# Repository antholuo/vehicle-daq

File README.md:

# vehicle-daq

Vehicle data-acquisition system: **ESP32-C6 sensor nodes** stream IMU and GPS over **ESP-NOW** to a **bridge**; the bridge forwards data over **USB** to a **Raspberry Pi**, which logs CSV, runs optional AHRS, and supports **track capture** (waypoint logging via a GPS-only “floating” node).

**note:** Correspondent REPLAY system is hosted here: https://github.com/Trotyl15/vehicle-replay

The two main software pieces are:

| Component | Location | Role |
|-----------|----------|------|
| **rpi_rx_rust** | [`sw/tools/rpi_rx_rust/`](sw/tools/rpi_rx_rust/) | Pi-side: COBS decoder, CSV logging, AHRS, track capture (GPIO or interactive). |
| **sensor_board_rev1_test** | [`sw/sensor_board/sensor_board_rev1_test/`](sw/sensor_board/sensor_board_rev1_test/) | Firmware for Rev1 DAQ nodes (sensor + floating) and for the bridge (devkit). |

---

## System overview

```mermaid
flowchart TB
  subgraph sensors["Sensor nodes"]
    SN["rev1_board<br/>IMU + GPS"]
  end

  subgraph bridge["Bridge (devkit)"]
    B["devkit_c<br/>Forward, TimeSync<br/>track heartbeats"]
  end

  subgraph host["Raspberry Pi"]
    R["rpi_rx_rust<br/>Logs, AHRS<br/>track capture"]
  end

  subgraph floating["Floating node"]
    F["sensorboard_floating<br/>GPS only"]
  end

  SN -->|"ESP-NOW (IMU, GPS, heartbeat)"| B
  B -->|"USB COBS (forwarded messages)"| R
  R -->|"TimeSync, Arm/End, RequestFloatingGps"| B
  B -->|"TrackCaptureArmed/Ended (pause TX)"| SN
  B -->|"RequestGpsCapture"| F
  F -->|"5× GPS reply"| B
  B -->|"heartbeat 0xFE (when armed)"| R
```

- **Sensor nodes** (`rev1_board`): Read IMU and GPS, send over ESP-NOW. When track capture is armed, they pause so the floating node’s packets aren’t dropped.
- **Bridge** (`devkit_c`): Receives ESP-NOW, assigns node IDs by MAC, forwards messages to the Pi over USB (COBS). Sends TimeSync to nodes; handles Arm/End track and RequestFloatingGps; when armed, sends a track-capture heartbeat (0xFE) to the Pi every 500 ms.
- **Floating node** (`sensorboard_floating`): GPS-only; on RequestGpsCapture it replies with the next 5 GPS samples for waypoint logging.
- **Pi** (`rpi_rx_rust`): Decodes COBS stream, writes raw CSV (and optional AHRS CSV). Can arm track capture, request floating GPS per waypoint, and write track files (`~/daq/tracks/<date>/<time>.csv`). Uses track heartbeats to auto-end capture if the bridge disappears; bridge auto-ends if the Pi disappears.

---

## Raspberry Pi (rpi_rx_rust)

- **Binaries**: `rpi_rx_rust` (CLI + serial), `rpi_rx_rust_gpio` (GPIO-only service), `rpi_rx_rust_track_test` (interactive track capture), `ahrs_postprocess`, `gps_extract`.
- **Default serial**: `/dev/ttyACM0`, 115200 baud (set `RPI_RX_SERIAL_PORT` if the bridge is on another port).
- **Logs**: `~/daq/logs/<date>/` (raw and AHRS); track files: `~/daq/tracks/<date>/`.
- **Track capture**: Arm → take location (request 5 GPS from floating node, average, append one row) → end. Heartbeat from bridge (0xFE) every 500 ms; 3 s without heartbeat or 2 s without USB from Pi triggers auto-end.

Full build and usage: **[sw/tools/rpi_rx_rust/README.md](sw/tools/rpi_rx_rust/README.md)**.

---

## Sensor board & bridge (sensor_board_rev1_test)

- **Binaries**: `rev1_board` (sensor node), `devkit_c` (bridge), `sensorboard_floating` (GPS-only for track capture).
- **Build** (from `sw/sensor_board/sensor_board_rev1_test/`):
  - Sensor: `cargo build --bin rev1_board` (optional `--features pos_center` etc.).
  - Bridge: `cargo build --bin devkit_c --no-default-features --features bridge`.
  - Floating: `cargo build --bin sensorboard_floating --no-default-features --features floating`.
- **HMI**: User LED (1 Hz) + NeoPixel (state/feedback). Bridge: 4× blink when armed; orange when sending request; green/rainbow on success/timeout. Floating: green breathing when idle with fix; orange when acquiring.

Full build, features, task model, and hardware init: **[sw/sensor_board/sensor_board_rev1_test/README.md](sw/sensor_board/sensor_board_rev1_test/README.md)**.

Other repos under `sw/`, `ee/`, and `vision/` may have their own READMEs.

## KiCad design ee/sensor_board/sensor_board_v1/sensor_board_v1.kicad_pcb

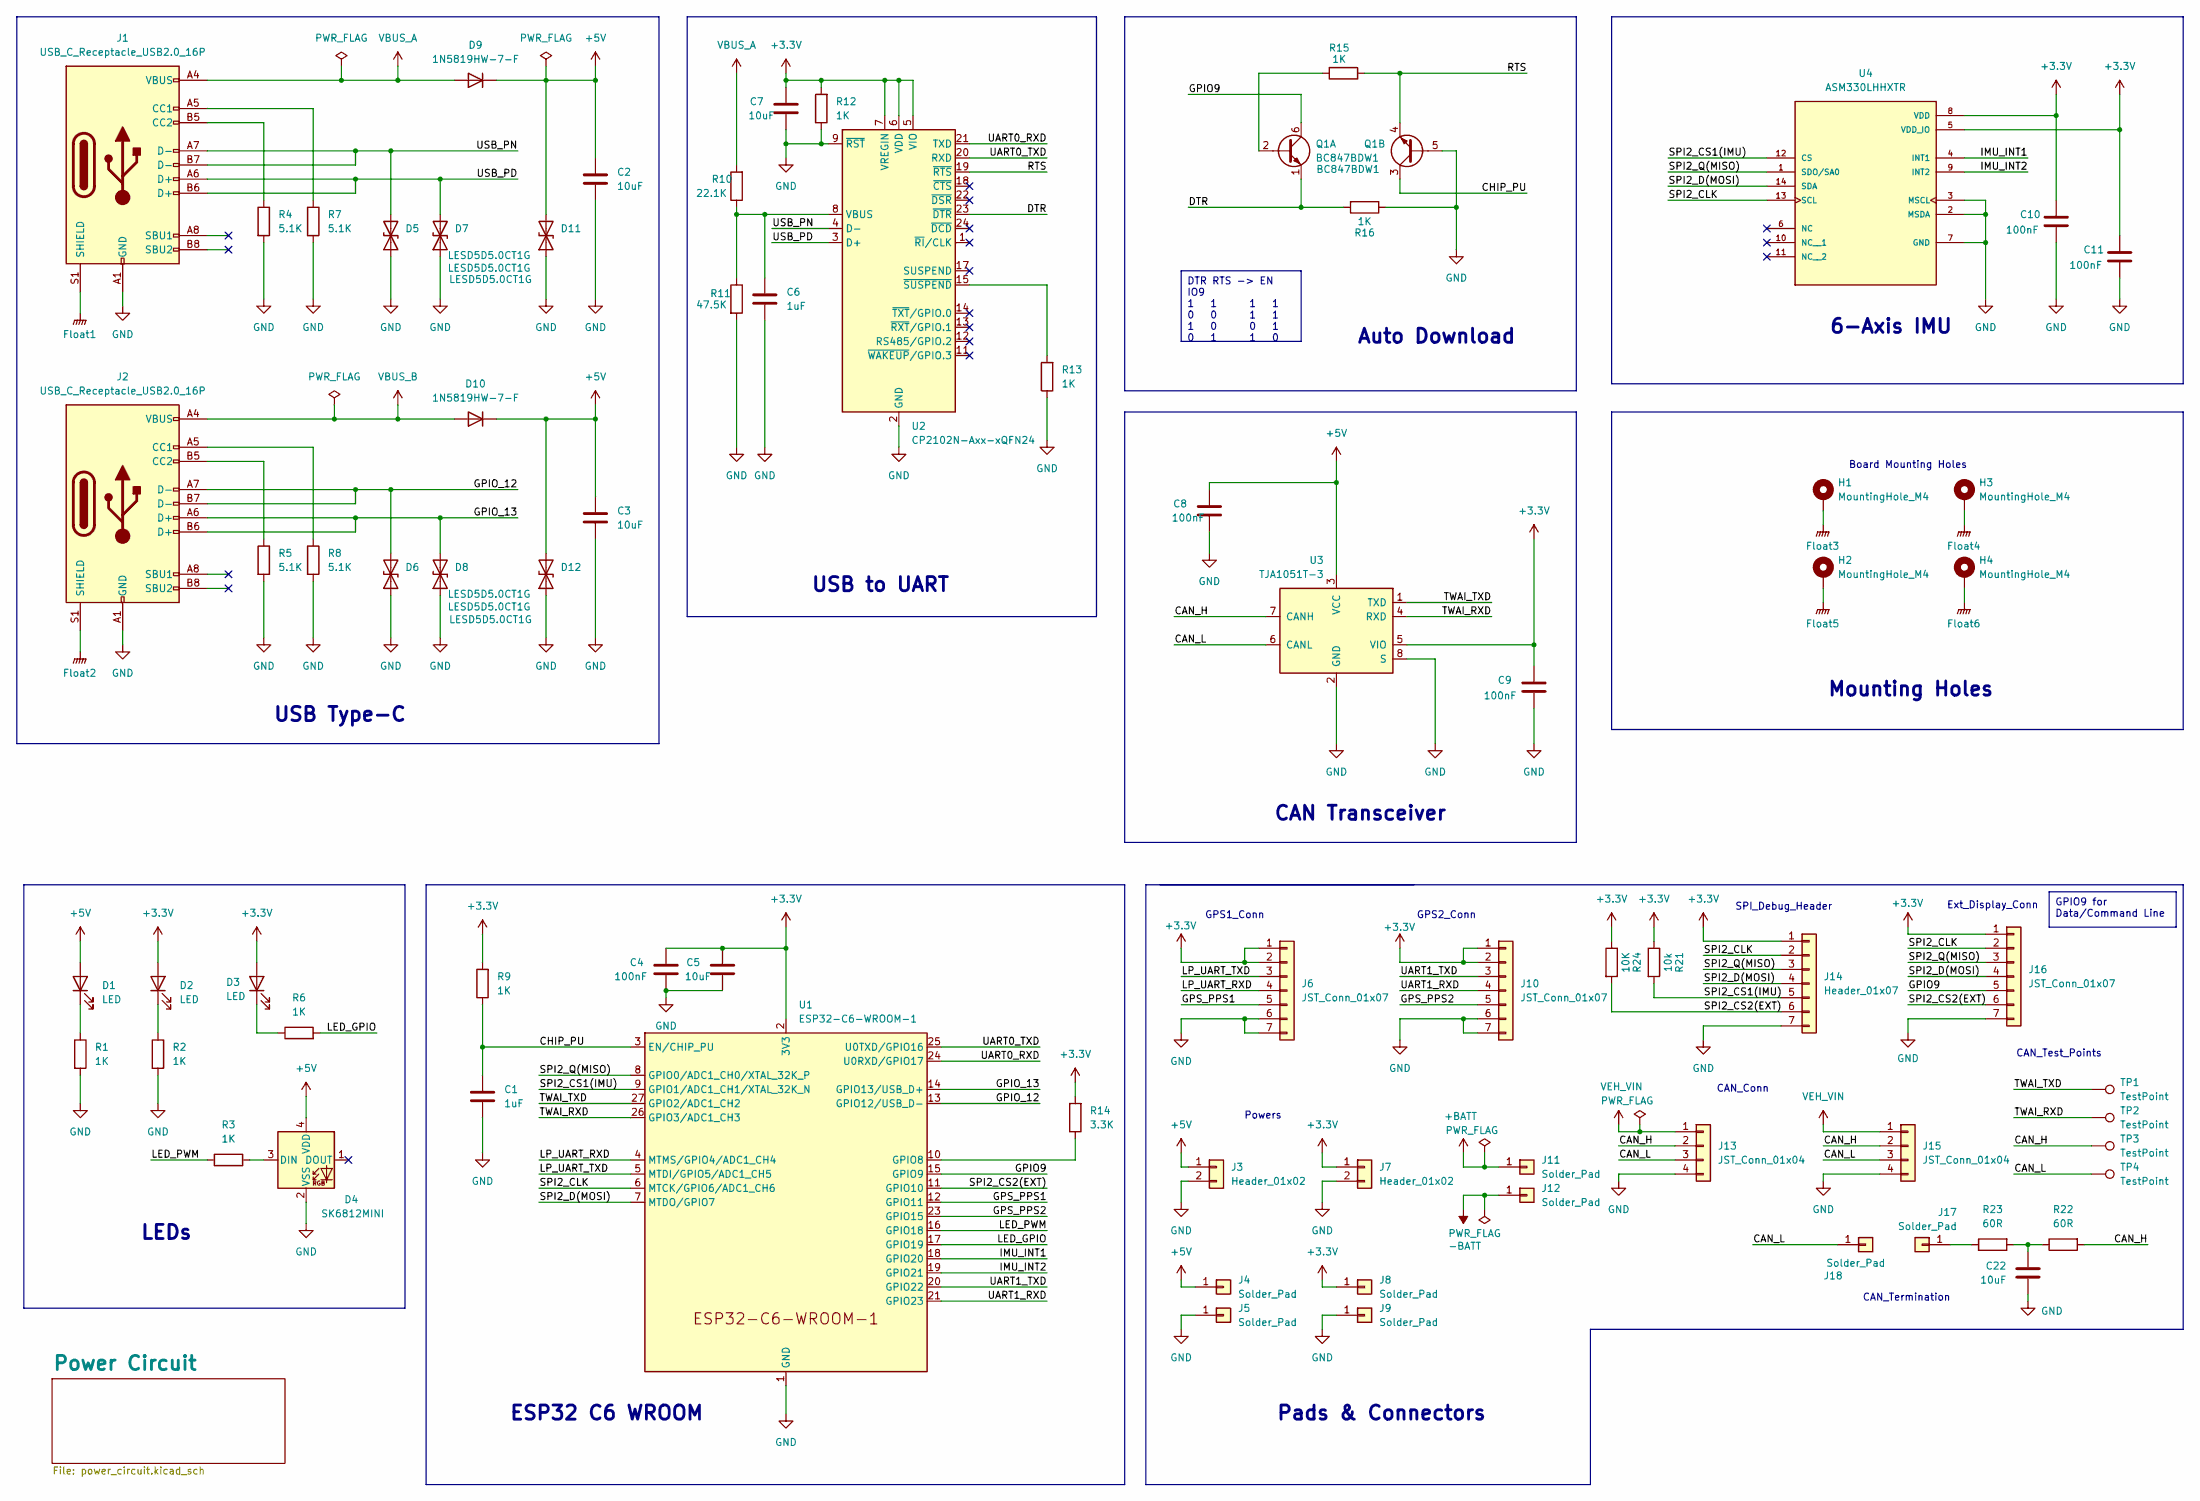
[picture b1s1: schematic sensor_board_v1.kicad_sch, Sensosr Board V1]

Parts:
C1, C6: 1uF; C_0603_1608Metric
C2, C3, C5, C7, C22: 10uF; C_0603_1608Metric
C4, C8, C9, C10, C11: 100nF; C_0603_1608Metric
D1, D2, D3: LED; LED_0603_1608Metric
D4: SK6812MINI; LED_SK6812MINI_PLCC4_3.5x3.5mm_P1.75mm
D5, D6, D7, D8, D11, D12: LESD5D5.0CT1G; D_0603_1608Metric
D9, D10: 1N5819HW-7-F; D_SOD-123
H1, H2, H3, H4: MountingHole_M4; MountingHole_4.3mm_M4_DIN965_Pad
J1, J2: USB_C_Receptacle_USB2.0_16P; USB_C_Receptacle_Palconn_UTC16-G
J3, J7: Header_01x02; PinHeader_1x02_P1.00mm_Vertical
J4, J5, J8, J9, J17, J18: Solder_Pad; SolderWirePad_1x01_SMD_1x2mm
J6, J10, J16: JST_Conn_01x07; JST_GH_SM07B-GHS-TB_1x07-1MP_P1.25mm_Horizontal
J11, J12: Solder_Pad; TestPoint_Pad_2.0x2.0mm
J13, J15: JST_Conn_01x04; JST_GH_SM04B-GHS-TB_1x04-1MP_P1.25mm_Horizontal
J14: Header_01x07; JST_GH_SM07B-GHS-TB_1x07-1MP_P1.25mm_Horizontal
Q1: BC847BDW1; SOT-363_SC-70-6
R1, R2, R3, R6, R9, R12, R13, R15, R16: 1K; R_0603_1608Metric
R4, R5, R7, R8: 5.1K; R_0603_1608Metric
R10: 22.1K; R_0603_1608Metric
R11: 47.5K; R_0603_1608Metric
R14: 3.3K; R_0603_1608Metric
R21: 10k; R_0603_1608Metric
R22, R23: 60R; R_0603_1608Metric
R24: 10K; R_0603_1608Metric
TP1, TP2, TP3, TP4: TestPoint; TestPoint_Pad_1.0x1.0mm
U1: ESP32-C6-WROOM-1
U2: CP2102N-Axx-xQFN24; QFN-24-1EP_4x4mm_P0.5mm_EP2.6x2.6mm
U3: TJA1051T-3; SOIC-8_3.9x4.9mm_P1.27mm
U4: ASM330LHHXTR; XDCR_ASM330LHHXTR; PARTREV 8

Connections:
+3.3V: C4.1, C5.1, C7.1, C9.1, C10.1, C11.1, D2.2 (A), D3.2 (A), J6.1, J6.2, J7.1, J8.1, J10.1, J10.2, J14.1, J16.1, R9.2, R12.2, R14.2, R21.1, R24.1, U1.2 (3V3), U2.5 (VIO), U2.6 (VDD), U2.7 (VREGIN), U3.5 (VIO), U4.5 (VDD_IO), U4.8 (VDD); also elsewhere on the board
+5V: C2.1, C3.1, C8.1, D1.2 (A), D4.4 (VDD), D9.1 (K), D10.1 (K), D11.2 (A2), D12.2 (A2), J3.1, J4.1, U3.3 (VCC); also elsewhere on the board
+BATT: J11.1; also elsewhere on the board
-BATT: J12.1; also elsewhere on the board
/CAN_H: J13.2, J15.2, R22.2, TP3.1, U3.7 (CANH)
/CAN_L: J13.3, J15.3, J18.1, TP4.1, U3.6 (CANL)
/CHIP_PU: C1.1, Q1.3 (C2), R9.1, U1.3 (EN/CHIP_PU)
/DTR: Q1.1 (E1), R16.2, U2.23 (~DTR)
/GPIO9: J16.5, Q1.6 (C1), U1.15 (GPIO9)
/GPIO_12: D6.2 (A2), J2.A7 (D-), J2.B7 (D-), U1.13 (GPIO12/USB_D-)
/GPIO_13: D8.2 (A2), J2.A6 (D+), J2.B6 (D+), U1.14 (GPIO13/USB_D+)
/GPS_PPS1: J6.5, U1.12 (GPIO11)
/GPS_PPS2: J10.5, U1.23 (GPIO15)
/IMU_INT1: U1.18 (GPIO20), U4.4 (INT1)
/IMU_INT2: U1.19 (GPIO21), U4.9 (INT2)
/LED_GPIO: R6.2, U1.17 (GPIO19)
/LED_PWM: R3.1, U1.16 (GPIO18)
/LP_UART_RXD: J6.4, U1.4 (MTMS/GPIO4/ADC1_CH4)
/LP_UART_TXD: J6.3, U1.5 (MTDI/GPIO5/ADC1_CH5)
/RTS: Q1.4 (E2), R15.1, U2.19 (~RTS)
/SPI2_CLK: J14.2, J16.2, U1.6 (MTCK/GPIO6/ADC1_CH6), U4.13 (SCL)
/SPI2_CS1(IMU): J14.5, R21.2, U1.9 (GPIO1/ADC1_CH1/XTAL_32K_N), U4.12 (CS)
/SPI2_CS2(EXT): J14.6, J16.6, R24.2, U1.11 (GPIO10)
/SPI2_D(MOSI): J14.4, J16.4, U1.7 (MTDO/GPIO7), U4.14 (SDA)
/SPI2_Q(MISO): J14.3, J16.3, U1.8 (GPIO0/ADC1_CH0/XTAL_32K_P), U4.1 (SDO/SA0)
/TWAI_RXD: TP2.1, U1.26 (GPIO3/ADC1_CH3), U3.4 (RXD)
/TWAI_TXD: TP1.1, U1.27 (GPIO2/ADC1_CH2), U3.1 (TXD)
/UART0_RXD: U1.24 (U0RXD/GPIO17), U2.21 (TXD)
/UART0_TXD: U1.25 (U0TXD/GPIO16), U2.20 (RXD)
/UART1_RXD: J10.4, U1.21 (GPIO23)
/UART1_TXD: J10.3, U1.20 (GPIO22)
/USB_PD: D7.2 (A2), J1.A6 (D+), J1.B6 (D+), U2.3 (D+)
/USB_PN: D5.2 (A2), J1.A7 (D-), J1.B7 (D-), U2.4 (D-)
Float1: J1.S1 (SHIELD)
Float2: J2.S1 (SHIELD)
Float3: H1.1
Float4: H3.1
Float5: H2.1
Float6: H4.1
GND: C1.2, C2.2, C3.2, C4.2, C5.2, C6.2, C7.2, C8.2, C9.2, C10.2, C11.2, C22.2, D4.2 (VSS), D5.1 (A1), D6.1 (A1), D7.1 (A1), D8.1 (A1), D11.1 (A1), D12.1 (A1), J1.A1 (GND), J1.A12 (GND), J1.B1 (GND), J1.B12 (GND), J2.A1 (GND), J2.A12 (GND), J2.B1 (GND), J2.B12 (GND), J3.2, J5.1, J6.6, J6.7, J7.2, J9.1, J10.6, J10.7, J13.4, J14.7, J15.4, J16.7, Q1.5 (B2), R1.2, R2.2, R4.2, R5.2, R7.2, R8.2, R11.2, R12.1, R13.1, R16.1, U1.1 (GND), U1.28 (GND), U1.29 (GND), U2.2 (GND), U2.9 (~RST), U2.25 (GND), U3.2 (GND), U3.8 (S), U4.2 (MSDA), U4.3 (MSCL), U4.7 (GND); also elsewhere on the board
unnamed: C22.1, R22.1, R23.2
unnamed: D1.1 (K), R1.1
unnamed: D2.1 (K), R2.1
unnamed: D3.1 (K), R6.1
unnamed: D4.3 (DIN), R3.2
unnamed: J1.A5 (CC1), R7.1
unnamed: J1.B5 (CC2), R4.1
unnamed: J2.A5 (CC1), R8.1
unnamed: J2.B5 (CC2), R5.1
unnamed: J17.1, R23.1
unnamed: Q1.2 (B1), R15.2
unnamed: R14.1, U1.10 (GPIO8)
unnamed: C6.1, R10.1, R11.1, U2.8 (VBUS)
unnamed: R13.2, U2.15 (~SUSPEND)
VBUS_A: D9.2 (A), J1.A4 (VBUS), J1.A9 (VBUS), J1.B4 (VBUS), J1.B9 (VBUS), R10.2
VBUS_B: D10.2 (A), J2.A4 (VBUS), J2.A9 (VBUS), J2.B4 (VBUS), J2.B9 (VBUS)
VEH_VIN: J13.1, J15.1; also elsewhere on the board

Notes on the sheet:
GPIO9 for Data/Command Line
DTR RTS -> EN IO9 1 1 1 1 0 0 1 1 1 0 0 1 0 1 1 0
GPS1_Conn
USB to UART
6-Axis IMU
ESP32 C6 WROOM
Auto Download
Mounting Holes
Powers
SPI_Debug_Header
Ext_Display_Conn
USB Type-C
Board Mounting Holes
GPS2_Conn
CAN Transceiver
CAN_Conn
CAN_Test_Points
LEDs
Pads & Connectors
CAN_Termination

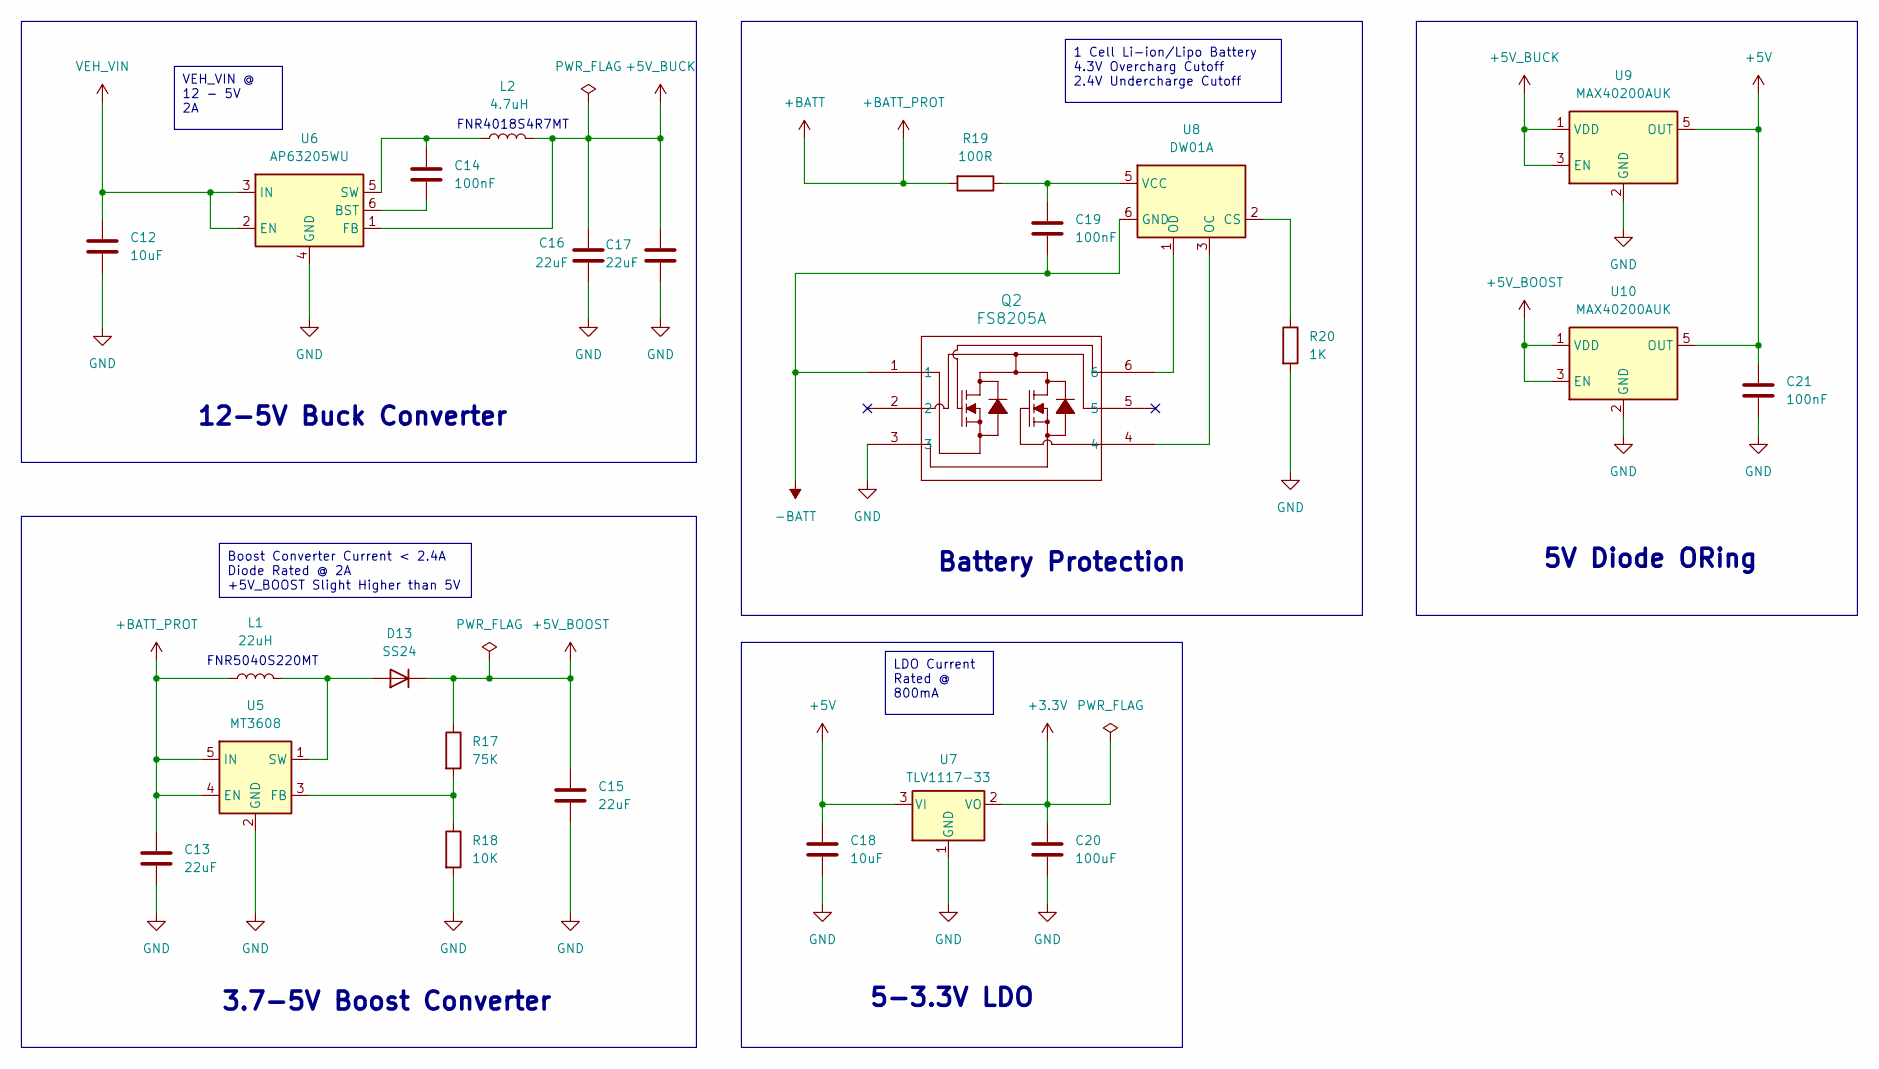
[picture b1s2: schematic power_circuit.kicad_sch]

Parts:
C12: 10uF; C_0805_2012Metric
C13, C15, C16, C17: 22uF; C_0805_2012Metric
C14, C19, C21: 100nF; C_0603_1608Metric
C18: 10uF; C_0603_1608Metric
C20: 100uF; C_0805_2012Metric
D13: SS24; D_SOD-123F
L1: 22uH; L_Changjiang_FNR5040S
L2: 4.7uH; L_Changjiang_FNR4018S
Q2: FS8205A; SOT-23-6L_TCP
R17: 75K; R_0603_1608Metric
R18: 10K; R_0603_1608Metric
R19: 100R; R_0603_1608Metric
R20: 1K; R_0603_1608Metric
U5: MT3608; SOT-23-6
U6: AP63205WU; TSOT-23-6
U7: TLV1117-33; SOT230P700X180-4N
U8: DW01A; SOT-23-6
U9, U10: MAX40200AUK; SOT-23-5

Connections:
+3.3V: C20.1, U7.2 (VO); also elsewhere on the board
+5V: C18.1, C21.1, U7.3 (VI), U9.5 (OUT), U10.5 (OUT); also elsewhere on the board
+5V_BOOST: C15.1, D13.1 (K), R17.1, U10.1 (VDD), U10.3 (EN)
+5V_BUCK: C16.1, C17.1, L2.2, U6.1 (FB), U9.1 (VDD), U9.3 (EN)
+BATT: C13.1, L1.1, R19.2, U5.4 (EN), U5.5 (IN); also elsewhere on the board
-BATT: C19.2, Q2.1, U8.6 (GND); also elsewhere on the board
GND: C12.2, C13.2, C15.2, C16.2, C17.2, C18.2, C20.2, C21.2, Q2.3, R18.2, R20.2, U5.2 (GND), U6.4 (GND), U7.1 (GND), U9.2 (GND), U10.2 (GND); also elsewhere on the board
unnamed: D13.2 (A), L1.2, U5.1 (SW)
unnamed: R17.2, R18.1, U5.3 (FB)
unnamed: C14.2, U6.6 (BST)
unnamed: C14.1, L2.1, U6.5 (SW)
unnamed: R20.1, U8.2 (CS)
unnamed: Q2.4, U8.3 (OC)
unnamed: Q2.6, U8.1 (OD)
unnamed: C19.1, R19.1, U8.5 (VCC)
VEH_VIN: C12.1, U6.2 (EN), U6.3 (IN); also elsewhere on the board

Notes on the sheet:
VEH_VIN @ 12 - 5V 2A
Boost Converter Current < 2.4A Diode Rated @ 2A +5V_BOOST Slight Higher than 5V
LDO Current Rated @ 800mA
1 Cell Li-ion/Lipo Battery 4.3V Overcharg Cutoff 2.4V Undercharge Cutoff
FNR4018S4R7MT
3.7-5V Boost Converter
5V Diode ORing
5-3.3V LDO
Battery Protection
FNR5040S220MT
12-5V Buck Converter

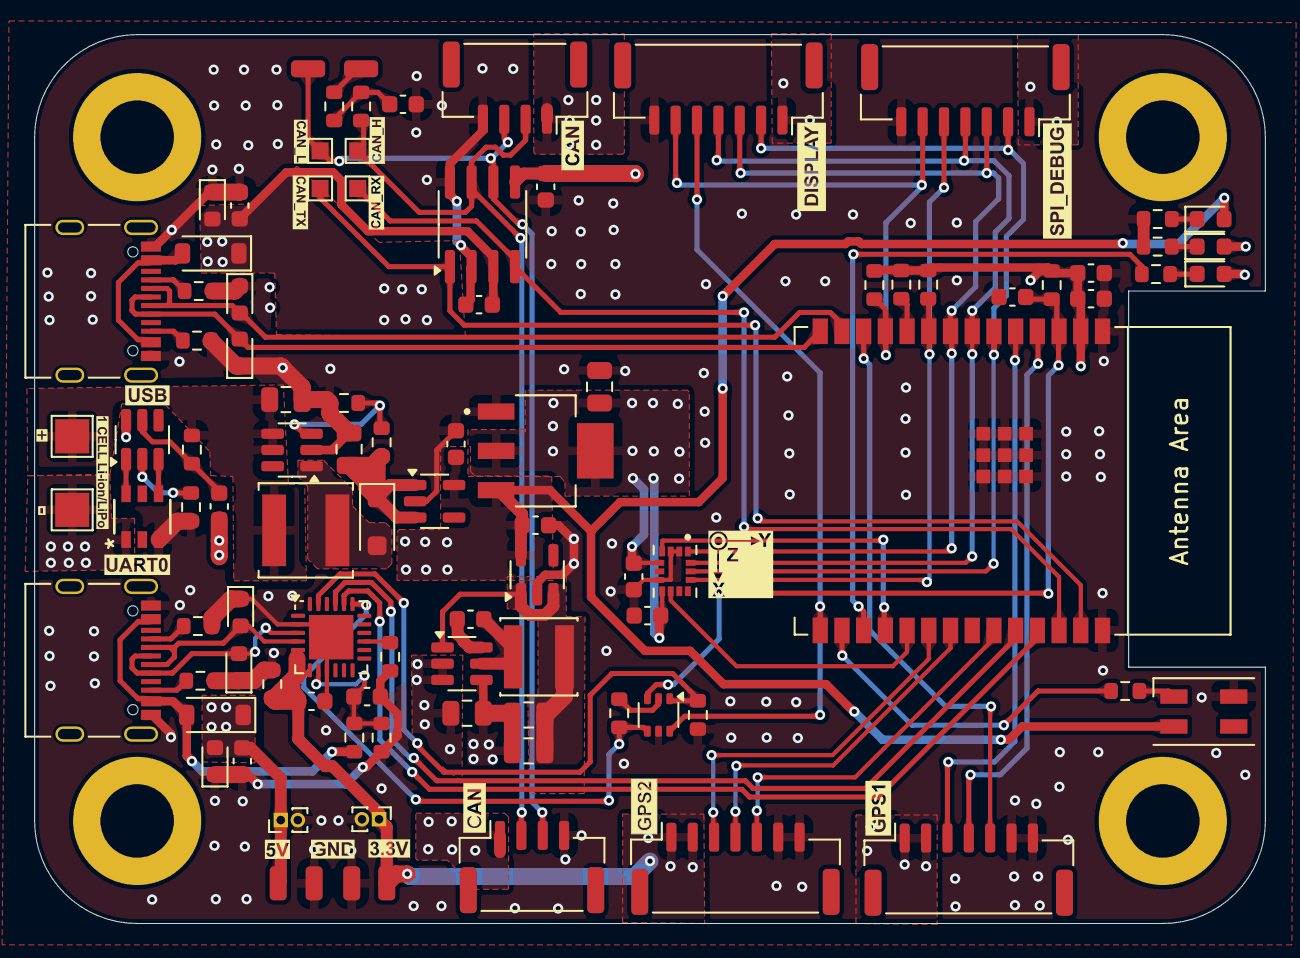
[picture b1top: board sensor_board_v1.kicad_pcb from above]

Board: 4 copper layers, 72.0 x 52.0 mm, 99 parts (0 on the bottom side), 61 nets.

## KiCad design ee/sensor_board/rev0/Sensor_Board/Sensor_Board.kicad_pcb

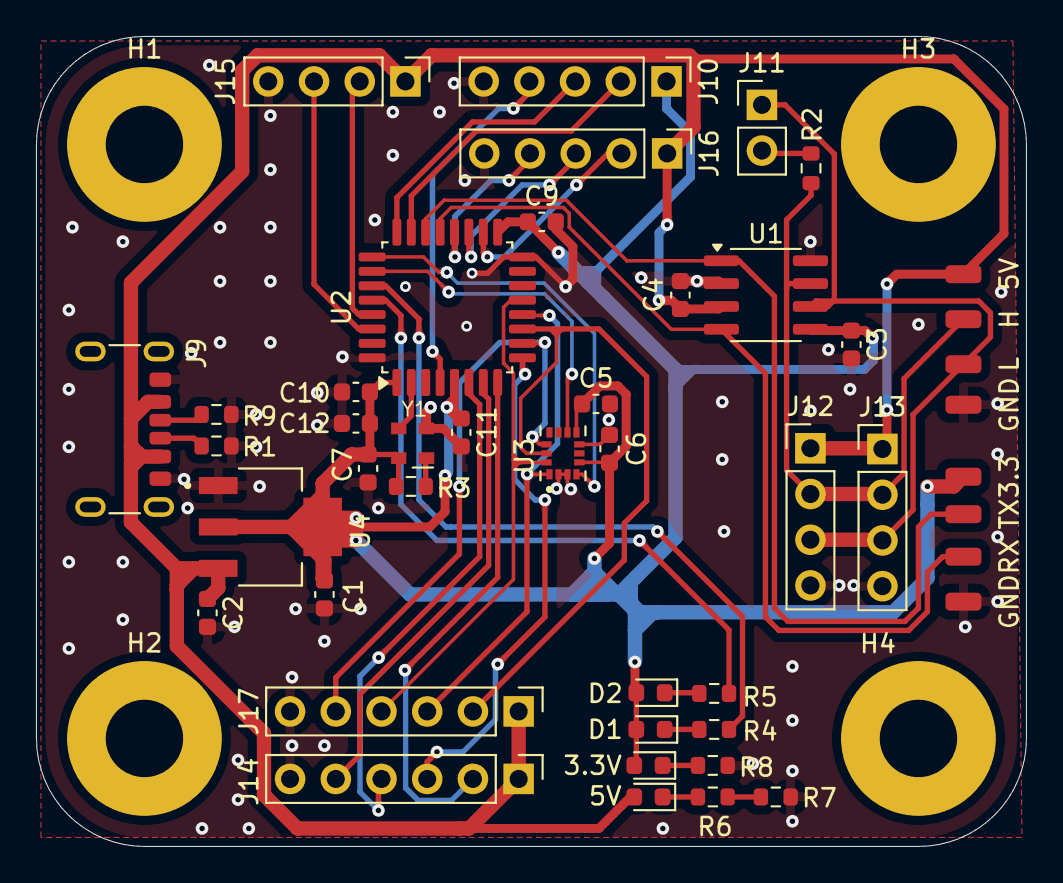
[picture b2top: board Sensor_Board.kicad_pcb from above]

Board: 4 copper layers, 55.0 x 45.0 mm, 50 parts (0 on the bottom side), 37 nets.

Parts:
3.3, 5V: Conn_01x01; SolderWirePad_1x01_SMD_1x2mm
3.3V, 5V#2: LED; LED_0603_1608Metric
C1: 100uF; C_0603_1608Metric
C2: 10uF; C_0603_1608Metric
C3, C4, C5, C6, C9, C10, C11: 100nF; C_0603_1608Metric
C7: 10nF; C_0603_1608Metric
C12: 1uF; C_0603_1608Metric
D1, D2: LED; LED_0603_1608Metric
GND: Conn_01x01; SolderWirePad_1x01_SMD_1x2mm
GND#2: Conn_01x01; SolderWirePad_1x01_SMD_1x2mm
H: Conn_01x01; SolderWirePad_1x01_SMD_1x2mm
H1, H2, H3, H4: MountingHole; MountingHole_4.3mm_M4_Pad
J9: USB_C_Receptacle_PowerOnly_6P; USB_C_Receptacle_GCT_USB4125-xx-x-0190_6P_TopMnt_Horizontal
J10, J16: Conn_01x05; PinHeader_1x05_P2.54mm_Vertical
J11: Conn_01x02; PinHeader_1x02_P2.54mm_Vertical
J12, J13, J15: Conn_01x04; PinHeader_1x04_P2.54mm_Vertical
J14, J17: Conn_01x06; PinHeader_1x06_P2.54mm_Vertical
L: Conn_01x01; SolderWirePad_1x01_SMD_1x2mm
R1, R9: 5.1K; R_0603_1608Metric
R2: 120R; R_0603_1608Metric
R3: 10k; R_0603_1608Metric
R4, R5: 1k; R_0603_1608Metric
R6, R7, R8: 1K; R_0603_1608Metric
RX: Conn_01x01; SolderWirePad_1x01_SMD_1x2mm
TX: Conn_01x01; SolderWirePad_1x01_SMD_1x2mm
U1: TJA1051T-3; SOIC-8_3.9x4.9mm_P1.27mm
U2: STM32F042K6Tx; LQFP-32_7x7mm_P0.8mm
U3: ASM330LHHXTR; XDCR_ASM330LHHXTR
U4: TLV1117-33; SOT230P700X180-4N
Y1: ASDDV-8.000MHZ-LR-T; Oscillator_SMD_Abracon_ASDMB-4Pin_2.5x2.0mm

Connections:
+3V3: 3.3.1, 3.3V.2 (A), C1.1, C3.1, C5.1, C6.1, C7.1, C9.1, C10.1, C11.1, C12.1, D1.2 (A), D2.2 (A), J10.1, R3.2, U1.5 (VIO), U2.1 (VDD), U2.5 (VDDA), U2.17 (VDDIO2), U3.5 (VDD_IO), U3.8 (VDD), U4.2 (VO), Y1.4 (VDD)
+5V: 5V.1, 5V#2.2 (A), C2.1, C4.1, J9.A9 (VBUS), J9.B9 (VBUS), J12.1, J13.1, J14.1, J15.1, J16.1, J17.1, U1.3 (VCC), U4.3 (VI)
/NRST: J10.4, U2.4 (NRST)
/RCC_OSC_IN: U2.2 (PF0), Y1.3 (OUTPUT)
/SWCLK: J10.3, U2.24 (PA14)
/SWDIO: J10.2, U2.23 (PA13)
CAN_H: H.1, J12.2, J13.2, R2.1, U1.7 (CANH)
CAN_L: J11.1, J12.3, J13.3, L.1, U1.6 (CANL)
CAN_RX: RX.1, U1.4 (RXD), U2.21 (PA11)
CAN_TX: TX.1, U1.1 (TXD), U2.22 (PA12)
GND: C1.2, C2.2, C3.2, C4.2, C5.2, C6.2, C7.2, C9.2, C10.2, C11.2, C12.2, GND.1, GND#2.1, J9.A12 (GND), J9.B12 (GND), J10.5, J12.4, J13.4, J14.6, J15.4, J16.5, J17.6, R1.2, R7.2, R8.2, R9.2, U1.2 (GND), U1.8 (S), U2.16 (VSS), U2.32 (VSSA), U3.2 (MSDA), U3.3 (MSCL), U3.7 (GND), U4.1 (GND), Y1.2 (GND/CASE)
GPIO_LED1: R4.2, U2.27 (PB4)
GPIO_LED2: R5.2, U2.28 (PB5)
IMU_CLK: J17.2, U2.11 (PA5), U3.13 (SCL)
IMU_CS: J17.5, U2.10 (PA4), U3.12 (CS)
IMU_IDO: J17.3, U2.12 (PA6), U3.1 (SDO/SA0)
IMU_SDI: J17.4, U2.13 (PA7), U3.14 (SDA)
unnamed: D1.1 (K), R4.1
unnamed: D2.1 (K), R5.1
unnamed: 3.3V.1 (K), R8.1
unnamed: 5V#2.1 (K), R6.1
unnamed: J9.A5 (CC1), R9.1
unnamed: J9.B5 (CC2), R1.1
unnamed: J11.2, R2.2
unnamed: R6.2, R7.1
unnamed: R3.1, Y1.1 (TRI_STATE)
TIM1_CH1: J16.2, U2.18 (PA8)
TIM1_CH2: J16.3, U2.19 (PA9)
TIM1_CH3: J16.4, U2.20 (PA10)
TIM2_CH1: U2.25 (PA15), U3.4 (INT1)
TIM2_CH2: U2.26 (PB3), U3.9 (INT2)
UART1_RX: J15.3, U2.30 (PB7)
UART1_TX: J15.2, U2.29 (PB6)
UART2_CTS: J14.4, U2.6 (PA0)
UART2_RTS: J14.5, U2.7 (PA1)
UART2_RX: J14.3, U2.9 (PA3)
UART2_TX: J14.2, U2.8 (PA2)

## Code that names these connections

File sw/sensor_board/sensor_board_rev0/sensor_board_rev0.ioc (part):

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Mcu.Name=STM32F042K(4-6)Tx
Mcu.Package=LQFP32
Mcu.UserName=STM32F042K6Tx
PA0.Mode=CTS_RTS
PA0.Signal=USART2_CTS
PA1.Mode=CTS_RTS
PA1.Signal=USART2_RTS
PA10.Signal=S_TIM1_CH3
PA11.Mode=CAN_Activate
PA11.Signal=CAN_RX
PA12.Mode=CAN_Activate
PA12.Signal=CAN_TX
PA13.Mode=Serial_Wire
PA13.Signal=SYS_SWDIO
PA14.Mode=Serial_Wire
PA14.Signal=SYS_SWCLK
PA15.Signal=S_TIM2_CH1_ETR
PA2.Mode=Asynchronous
PA2.Signal=USART2_TX
PA3.Mode=Asynchronous
PA3.Signal=USART2_RX
PA4.GPIOParameters=GPIO_Label
PA4.GPIO_Label=SPI_CS
PA4.Signal=GPIO_Output
PA5.GPIOParameters=GPIO_Speed
PA5.GPIO_Speed=GPIO_SPEED_FREQ_MEDIUM
PA5.Mode=Full_Duplex_Master
PA5.Signal=SPI1_SCK
PA6.GPIOParameters=GPIO_Speed,GPIO_PuPd
PA6.GPIO_PuPd=GPIO_PULLDOWN
PA6.GPIO_Speed=GPIO_SPEED_FREQ_MEDIUM
PA6.Mode=Full_Duplex_Master
PA6.Signal=SPI1_MISO
PA7.GPIOParameters=GPIO_Speed
PA7.GPIO_Speed=GPIO_SPEED_FREQ_MEDIUM
PA7.Mode=Full_Duplex_Master
PA7.Signal=SPI1_MOSI
PA8.Signal=S_TIM1_CH1
PA9.Signal=S_TIM1_CH2
PB3.Signal=S_TIM2_CH2
PB4.GPIOParameters=GPIO_Label
PB4.GPIO_Label=GPIO_LED1
PB4.Signal=GPIO_Output
PB5.GPIOParameters=GPIO_Label
PB5.GPIO_Label=GPIO_LED2
PB5.Signal=GPIO_Output
PB6.GPIOParameters=GPIO_Speed,GPIO_PuPd
PB6.GPIO_PuPd=GPIO_PULLUP
PB6.GPIO_Speed=GPIO_SPEED_FREQ_MEDIUM
PB6.Mode=Asynchronous
PB6.Signal=USART1_TX
PB7.GPIOParameters=GPIO_Speed,GPIO_PuPd
PB7.GPIO_PuPd=GPIO_PULLUP
PB7.GPIO_Speed=GPIO_SPEED_FREQ_MEDIUM
PB7.Mode=Asynchronous
PB7.Signal=USART1_RX
PF0-OSC_IN.Mode=HSE-External-Oscillator
PF0-OSC_IN.Signal=RCC_OSC_IN
PF1-OSC_OUT.Mode=HSE-External-Oscillator
PF1-OSC_OUT.Signal=RCC_OSC_OUT
RCC.SYSCLKFreq_VALUE=48000000
RCC.SYSCLKSource=RCC_SYSCLKSOURCE_PLLCLK
board=custom

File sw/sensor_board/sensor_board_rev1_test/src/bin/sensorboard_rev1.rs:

#![no_std]
#![no_main]
#![deny(
    clippy::mem_forget,
    reason = "mem::forget is generally not safe to do with esp_hal types, especially those \
    holding buffers for the duration of a data transfer."
)]

#[cfg(any(feature = "hmi", feature = "imu"))]
use embassy_embedded_hal::shared_bus::asynch::spi::SpiDevice;
#[cfg(any(feature = "hmi", feature = "imu"))]
use embassy_sync::mutex::Mutex;
#[allow(unused_imports)]
use log::{debug, error, info, trace, warn};
#[cfg(any(feature = "hmi", feature = "imu"))]
use static_cell::StaticCell;

use esp_alloc as _;

#[cfg(feature = "hmi")]
use sensor_board_rev1_test::hmi::neopixel;
use sensor_board_rev1_test::{BoardPeripherals, app::app_run};
#[cfg(feature = "wifi")]
use sensor_board_rev1_test::{EspNowMode, WifiResources};
#[cfg(any(feature = "hmi", feature = "imu"))]
use sensor_board_rev1_test::{SharedSpiBus, SharedSpiDevice};

#[cfg(any(feature = "hmi", feature = "imu"))]
static SPI_BUS: StaticCell<SharedSpiBus> = StaticCell::new();

#[panic_handler]
fn panic(_: &core::panic::PanicInfo) -> ! {
    loop {}
}

// This creates a default app-descriptor required by the esp-idf bootloader.
// For more information see: <https://docs.espressif.com/projects/esp-idf/en/stable/esp32/api-reference/system/app_image_format.html#application-description>
esp_bootloader_esp_idf::esp_app_desc!();

fn init_heap() {
    const HEAP_SIZE: usize = 128 * 1024; // arbitrary size
    static mut HEAP: [u8; HEAP_SIZE] = [0; HEAP_SIZE];

    unsafe {
        esp_alloc::HEAP.add_region(esp_alloc::HeapRegion::new(
            // HEAP.as_ptr() as *mut u8,
            &HEAP[0] as *const u8 as *mut u8,
            HEAP_SIZE,
            esp_alloc::MemoryCapability::Internal.into(),
        ));
    }
}

pub struct SensorBoardRev1 {
    #[cfg(feature = "hmi")]
    pub user_led: Option<esp_hal::gpio::Output<'static>>,
    #[cfg(feature = "hmi")]
    pub neopixel: Option<neopixel::NeoPixel<'static>>,
    #[cfg(feature = "hmi")]
    pub disp_spi: Option<SharedSpiDevice>,
    #[cfg(feature = "imu")]
    pub imu_spi: Option<SharedSpiDevice>,
    #[cfg(feature = "gps")]
    pub gps2_uart: Option<esp_hal::uart::Uart<'static, esp_hal::Async>>,
    #[cfg(feature = "wifi")]
    pub wifi: Option<WifiResources>,
}

impl SensorBoardRev1 {
    pub fn from_peripherals(peripherals: esp_hal::peripherals::Peripherals) -> Self {
        // RTOS bootstrap
        let timg0 = esp_hal::timer::timg::TimerGroup::new(peripherals.TIMG0);
        let software_interrupt =
            esp_hal::interrupt::software::SoftwareInterruptControl::new(peripherals.SW_INTERRUPT);

        esp_rtos::start(timg0.timer0, software_interrupt.software_interrupt0);
        debug!(">>> building SensorBoardRev1");

        // HMI peripherals
        #[cfg(feature = "hmi")]
        let user_led = esp_hal::gpio::Output::new(
            peripherals.GPIO19,
            esp_hal::gpio::Level::High,
            esp_hal::gpio::OutputConfig::default(),
        );

        let rmt = esp_hal::rmt::Rmt::new(peripherals.RMT, esp_hal::time::Rate::from_mhz(80))
            .unwrap()
            .into_async();
        let neopixel = neopixel::NeoPixel::new(rmt.channel0, peripherals.GPIO18);

        // let gps2_uart_config = esp_hal::uart::Config::default().with_baudrate(9600);
        let gps2_uart_config = esp_hal::uart::Config::default().with_baudrate(460800);
        info!("baudrate for gps2_uart_set");
        let gps2_uart = esp_hal::uart::Uart::new(peripherals.UART1, gps2_uart_config)
            .unwrap()
            .with_rx(peripherals.GPIO23)
            .with_tx(peripherals.GPIO22)
            .into_async();

        let spi_config = esp_hal::spi::master::Config::default()
            .with_frequency(esp_hal::time::Rate::from_khz(100))
            .with_mode(esp_hal::spi::Mode::_0);
        let spi2 = esp_hal::spi::master::Spi::new(peripherals.SPI2, spi_config)
            .unwrap()
            .with_sck(peripherals.GPIO6)
            .with_mosi(peripherals.GPIO7)
            .with_miso(peripherals.GPIO0)
            .into_async();
        let spi_bus = SPI_BUS.init(Mutex::new(spi2));
        let imu_spi2_cs = esp_hal::gpio::Output::new(
            peripherals.GPIO1,
            esp_hal::gpio::Level::High,
            esp_hal::gpio::OutputConfig::default(),
        );
        let disp_spi2_cs = esp_hal::gpio::Output::new(
            peripherals.GPIO10,
            esp_hal::gpio::Level::High,
            esp_hal::gpio::OutputConfig::default(),
        );
        let imu_spi_device = SpiDevice::new(spi_bus, imu_spi2_cs);
        let disp_spi_device = SpiDevice::new(spi_bus, disp_spi2_cs);

        // WiFi initialization
        #[cfg(feature = "wifi")]
        let wifi = match esp_radio::wifi::new(peripherals.WIFI, esp_radio::wifi::Config::default())
        {
            Ok((mut wifi_controller, interfaces)) => {
                info!("WiFi initialized successfully");
                if let Err(e) = wifi_controller.set_mode(esp_radio::wifi::WifiMode::Station) {
                    warn!("Failed to set WiFi mode: {:?}", e);
                    None
                } else if let Err(e) = wifi_controller.start() {
                    warn!("Failed to start WiFi controller: {:?}", e);
                    None
                } else {
                    Some(WifiResources {
                        controller: wifi_controller,
                        esp_now: interfaces.esp_now,
                    })
                }
            }
            Err(e) => {
                warn!("WiFi initialization failed: {:?}", e);
                None
            }
        };

        debug!(">>> SensorBoardRev1 returned things correctly");
        Self {
            #[cfg(feature = "hmi")]
            user_led: Some(user_led),
            #[cfg(feature = "hmi")]
            neopixel: Some(neopixel),
            #[cfg(feature = "hmi")]
            disp_spi: Some(disp_spi_device),
            #[cfg(feature = "imu")]
            imu_spi: Some(imu_spi_device),
            #[cfg(feature = "gps")]
            gps2_uart: Some(gps2_uart),
            #[cfg(feature = "wifi")]
            wifi,
        }
    }
}

impl BoardPeripherals for SensorBoardRev1 {
    #[cfg(feature = "hmi")]
    fn take_user_led(&mut self) -> esp_hal::gpio::Output<'static> {
        trace!("user led take called");
        self.user_led.take().expect("user LED already taken")
    }

    #[cfg(feature = "hmi")]
    fn take_neopixel(&mut self) -> neopixel::NeoPixel<'static> {
        trace!("neopixel take called");
        self.neopixel.take().expect("NeoPixel already taken")
    }

    #[cfg(feature = "hmi")]
    fn take_disp_spi_device(&mut self) -> SharedSpiDevice {
        trace!("disp_spi_device take called");
        self.disp_spi
            .take()
            .expect("DisplaySPI device already taken")
    }

    #[cfg(feature = "imu")]
    fn take_imu_spi_device(&mut self) -> SharedSpiDevice {
        trace!("imu_spi_device take called");
        self.imu_spi.take().expect("ImuSPI device already taken")
    }

    #[cfg(feature = "gps")]
    fn take_gps2_uart(&mut self) -> esp_hal::uart::Uart<'static, esp_hal::Async> {
        trace!("gps2_uart take called");
        self.gps2_uart.take().expect("gps2_uart already taken")
    }

    #[cfg(feature = "wifi")]
    fn take_wifi(&mut self) -> Option<WifiResources> {
        trace!("wifi take called");
        self.wifi.take()
    }

    #[cfg(feature = "wifi")]
    fn espnow_mode(&self) -> EspNowMode {
        // Sensor board sends data to bridge
        EspNowMode::Sender
    }
}

#[esp_rtos::main]
async fn main(spawner: embassy_executor::Spawner) {
    esp_println::logger::init_logger(log::LevelFilter::Info);
    // esp_println::logger::init_logger_from_env();

    init_heap();

    let config = esp_hal::Config::default().with_cpu_clock(esp_hal::clock::CpuClock::max());
    let peripherals = esp_hal::init(config);

    info!("Configuration complete - running app?");
    app_run(spawner, SensorBoardRev1::from_peripherals(peripherals)).await;
    loop {
        embassy_time::Timer::after_secs(1).await
    }
}

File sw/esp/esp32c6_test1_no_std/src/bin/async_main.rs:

#![no_std]
#![no_main]

use embassy_executor::Spawner;
use embassy_time::{Duration, Timer};
use esp_backtrace as _;
use esp_hal::clock::CpuClock;
use log::info;

use embassy_sync::{blocking_mutex::raw::NoopRawMutex, signal::Signal};
use esp_hal::{
    gpio::lp_io::{LowPowerInput, LowPowerOutput},
    load_lp_code,
    lp_core::{LpCore, LpCoreWakeupSource},
    main,
    rmt::Rmt,
    time::Rate,
    uart::{lp_uart::LpUart, AtCmdConfig, Config, RxConfig, Uart, UartRx, UartTx},
    Async,
};
use esp_hal_smartled::{buffer_size_async, SmartLedsAdapterAsync};
use smart_leds::{
    brightness, gamma,
    hsv::{hsv2rgb, Hsv},
    SmartLedsWriteAsync, RGB8,
};

extern crate alloc;

const READ_BUF_SIZE: usize = 64;
const AT_CMD: u8 = 0x04;

#[embassy_executor::task]
async fn writer(mut tx: UartTx<'static, Async>, signal: &'static Signal<NoopRawMutex, usize>) {
    use core::fmt::Write;
    embedded_io_async::Write::write(
        &mut tx,
        b"Hello async serial. Enter something ended with EOT (CTRL-D).\r\n",
    )
    .await
    .unwrap();
    embedded_io_async::Write::flush(&mut tx).await.unwrap();
    loop {
        let bytes_read = signal.wait().await;
        signal.reset();
        write!(&mut tx, "\r\n-- received {} bytes --\r\n", bytes_read).unwrap();
        embedded_io_async::Write::flush(&mut tx).await.unwrap();
    }
}

#[embassy_executor::task]
async fn reader(mut rx: UartRx<'static, Async>, signal: &'static Signal<NoopRawMutex, usize>) {
    const MAX_BUFFER_SIZE: usize = 10 * READ_BUF_SIZE + 16;

    let mut rbuf: [u8; MAX_BUFFER_SIZE] = [0u8; MAX_BUFFER_SIZE];
    let mut offset = 0;
    loop {
        let r = embedded_io_async::Read::read(&mut rx, &mut rbuf[offset..]).await;
        match r {
            Ok(len) => {
                offset += len;
                esp_println::println!("Read: {len}, data: {:?}", &rbuf[..offset]);
                offset = 0;
                signal.signal(len);
            }
            Err(e) => esp_println::println!("RX Error: {:?}", e),
        }
    }
}

#[esp_hal_embassy::main]
async fn main(spawner: Spawner) {
    // generator version: 0.2.2

    let config = esp_hal::Config::default().with_cpu_clock(CpuClock::max());
    let peripherals = esp_hal::init(config);

    esp_alloc::heap_allocator!(size: 72 * 1024);

    esp_println::logger::init_logger_from_env();

    let timer0 = esp_hal::timer::systimer::SystemTimer::new(peripherals.SYSTIMER);
    esp_hal_embassy::init(timer0.alarm0);

    info!("Embassy initialized!");

    let timg_0 = esp_hal::timer::timg::TimerGroup::new(peripherals.TIMG0);
    let timg_1 = esp_hal::timer::timg::TimerGroup::new(peripherals.TIMG1);

    // wifi init
    // let _init = esp_wifi::init(
    //     timg_0.timer0,
    //     esp_hal::rng::Rng::new(peripherals.RNG),
    //     peripherals.RADIO_CLK,
    // )
    // .unwrap();

    // Turn on that stupid RGB LED
    // esp_hal_embassy::init(timg_1.timer0);

    // Configure RMT (Remote Control Transceiver) peripheral globally
    // <https://docs.espressif.com/projects/esp-idf/en/stable/esp32/api-reference/peripherals/rmt.html>
    let rmt: Rmt<'_, esp_hal::Async> = {
        let frequency: Rate = { Rate::from_mhz(80) };
        Rmt::new(peripherals.RMT, frequency)
    }
    .expect("Failed to initialize RMT")
    .into_async();

    // We use one of the RMT channels to instantiate a `SmartLedsAdapterAsync` which can
    // be used directly with all `smart_led` implementations
    let rmt_channel = rmt.channel0;
    let rmt_buffer = [0_u32; buffer_size_async(1)];

    let mut led: SmartLedsAdapterAsync<_, 25> =
        { SmartLedsAdapterAsync::new(rmt_channel, peripherals.GPIO8, rmt_buffer) };
    let mut color = Hsv {
        hue: 0,
        sat: 255,
        val: 255,
    };

    let mut hue_val: u8 = 0;
    let mut sat_val: u8 = 128;
    let mut data = RGB8 {
        r: 0,
        g: 128,
        b: 255,
    };
    let level = 10;

    // UART test setup
    //
    let lp_pin = LowPowerOutput::new(peripherals.GPIO1);

    // let (lp_uart_rx_pin, lp_uart_tx_pin) = (peripherals.GPIO4, peripherals.GPIO5);
    let lp_uart_config = Config::default()
        .with_rx(RxConfig::default().with_fifo_full_threshold(READ_BUF_SIZE as u16));

    let mut lp_uart = LpUart::new(
        peripherals.LP_UART,
        lp_uart_config,
        LowPowerOutput::new(peripherals.GPIO5),
        LowPowerInput::new(peripherals.GPIO4),
    );

    let mut lp_core = LpCore::new(peripherals.LP_CORE);
    lp_core.stop();
    info!("lp_core stopped");

    let lp_core_code = load_lp_code!(
        // "../esp-hal/esp-lp-hal/target/riscv32imac-unknown-none-elf/debug/examples/blinky"
        "../esp32c6_test1_no_std_lpcore/target/riscv32imac-unknown-none-elf/debug/esp32c6_test1_no_std_lpcore"
    );

    lp_core_code.run(&mut lp_core, LpCoreWakeupSource::HpCpu, lp_pin, lp_uart);
    info!("lp_core run");

    // let mut lp_uart = Uart::new(peripherals.LP_UART, lp_uart_config)
    //     .unwrap()
    //     .with_tx(lp_uart_tx_pin)
    //     .with_rx(lp_uart_rx_pin)
    // .into_async();
    // TODO: Spawn some tasks
    let _ = spawner;

    loop {
        // info!("Hello world!");
        color.hue = hue_val;
        // color.sat = sat_val;

        data = hsv2rgb(color);

        // data.r = data.r.wrapping_add(1);
        // data.b = data.b.wrapping_add(1);
        // data.g = data.g.wrapping_add(1);

        led.write(brightness(gamma([data].into_iter()), level))
            .await
            .unwrap();

        hue_val = hue_val.wrapping_add(1);

        if hue_val >= 255 {
            sat_val = sat_val.wrapping_add(3);
        } else if hue_val <= 0 {
        }
        let data = (0x5000_2000) as *mut u32;
        info!("Current {:x}           \u{000d}", unsafe {
            data.read_volatile()
        });

        Timer::after(Duration::from_secs(1)).await;
    }

    // for inspiration have a look at the examples at https://github.com/esp-rs/esp-hal/tree/v0.23.1/examples/src/bin
}

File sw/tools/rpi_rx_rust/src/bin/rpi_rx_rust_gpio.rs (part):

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        let postprocess_path = log_dir.join(format!("{}_postprocess.csv", time_str));

        info!(
            "Starting session: raw={}, postprocess={} (GPIO11={}, GPIO19={})",
            raw_path.display(),
            with_ahrs,
            gpio11_high,
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                Ok(v) => v,
                Err(_) => return true,
            };
            let gpio11 = values[0];
            let gpio19 = values[1];
            let gpio26 = values[2];
            let gpio10 = values[3];
            let gpio9 = values[4];

            if gpio26 && !video_recording.get() {
                video_recording.set(start_video_recording(&session_start));
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            }

            // Track capture: IO10 rising = new track file (arm); IO10 falling = end; IO9 rising = take location
            if gpio10 && !prev_track_arm.get() {
                let dir = track_dir_for_today();
                if let Ok(()) = fs::create_dir_all(&dir) {
                    let time_str = Local::now().format("%H-%M-%S").to_string();
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                        info!("Track capture armed: {}", path.display());
                    }
                }
            } else if !gpio10 && prev_track_arm.get() {
                timesync_sender.send_end_track();
            }
            prev_track_arm.set(gpio10);

            if gpio9 && !prev_track_capture.get() && track_file.borrow().is_some() {
                timesync_sender.request_floating_gps_capture();
                info!("Track capture: requested floating GPS (IO9 rising)");
            }
            prev_track_capture.set(gpio9);

            let active = gpio11 || gpio19;
            !active
        };

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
